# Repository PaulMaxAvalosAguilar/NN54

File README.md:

# Encoder2

Connecting science and technology with sport

If you want to achive change you must get power.Objectively know what you do, to control what you get, don't let things happen to you, make things happen.
Be stronger at any weight.

We understand that power is the only way to achieve change. Objectively know what you do, to control what you get. Be stronger at any weight

Incremental Optical Encoder

Project currently being worked by

Paul Max Avalos Aguilar

In the aiming of building an optical incremental encoder for vbt trainning

STUDIES THAT CONFIRM RELATIONSHIP BETWEEN VELOCITY AND %RM
Movement Velocity as a Measure of Loading Intensity in Resistance Training
https://www.researchgate.net/publication/41549227_Movement_Velocity_as_a_Measure_of_Loading_Intensity_in_Resistance_Training
There's a load-velocity relationship regardless of individual relative strength. These results confirm an inextricable relationshipbetween relative load and MPV:

1) evaluate maximal strength without the need to perform a 1RM test, or test of maximum number of repetitions to failure (XRM)
2) determine the %1RM that is being used as soon as the first repetition with any given load is performed
3) prescribe and monitor training load according to velocity, instead of percentages of 1RM or XRM.

STUDIES THAT CONFIRM RELATIONSHIP BETWEEN VELOCITY LOSS AND FATIGUE
Effect of loading on unintentional lifting velocity declines during single sets of repetitions to failure during upper and lower extremity muscle actions.
https://www.ncbi.nlm.nih.gov/pubmed/16944400
While average repetition velocity was recorded, a pattern of reduciton in the average velocity achieved during each repetition
was found.
This pattern of average velocity reduction indicates that for a given muscle action fatigue develops between each rep in a
given set in the form of velocity loss

Velocity Loss as a Variable for Monitoring Resistance Exercise
https://www.researchgate.net/publication/313686918_Velocity_Loss_as_a_Variable_for_Monitoring_Resistance_Exercise
There is a very close relationship was found between the relative loss of velocity in a set and the percentage of performed repetitions. Moreover, the percentage of performed repetitions for a given velocity loss showed a high absolute reliability. 

Movement velocity as a measure of level of effort during resistance exercise
https://www.researchgate.net/publication/318150104_Movement_velocity_as_a_measure_of_level_of_effort_during_resistance_exercise
By monitoring repetition velocity one can estimate with high accuracy the proximity of muscle failure and, therefore, to more objectively quantify the level of effort and fatigue being incurred during resistance training.

STUDIES THAT CONFIRM DIFFERENT FATIGUE PERCENTAGES TO GAINS STRENGTH
RESEARCHED APPLICATIONS OF VELOCITY BASED STRENGTH TRAINING
https://pdfs.semanticscholar.org/5f96/79c3f0f2d34478121d7cc33a50eb84dafb7a.pdf
minimizing velocity loss to an inferior to 20 percent can positively influence muscular strength, velocity losses of 35 percent an more can increase metabolites which
might produce longer recovery times

STUDIES THAT CONFIRM LIFTING AT MAX INTENDED SPEED PROVIDES BETTER ADAPTATIONS
Maximal intended velocity training induces greater gains in bench press performance than deliberately slower half-velocity training.
https://www.ncbi.nlm.nih.gov/pubmed/24734902
Lifting a given weight at maximum intended velocity provides significantly greater strength gains.
Strength gains can be maximised when repetitions are performed at maximal intended velocity

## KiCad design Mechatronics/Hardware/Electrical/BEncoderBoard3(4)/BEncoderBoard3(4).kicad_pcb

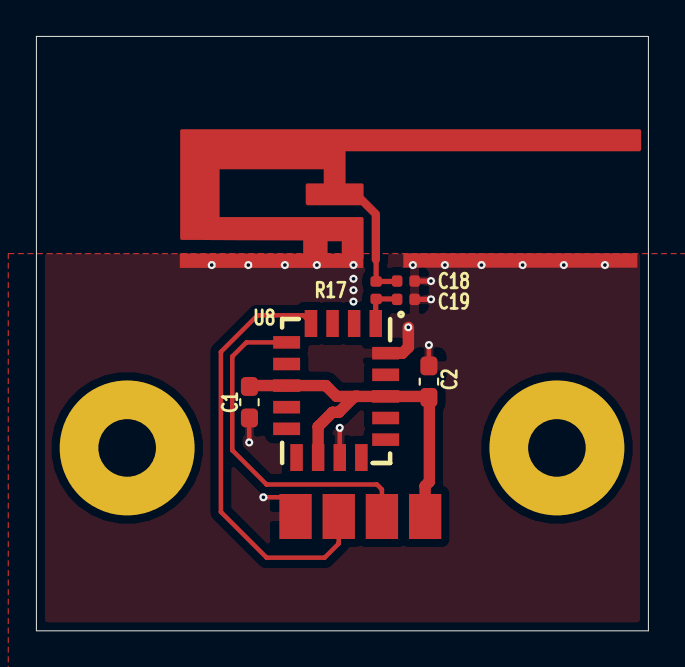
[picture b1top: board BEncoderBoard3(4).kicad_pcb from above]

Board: 4 copper layers, 34.0 x 33.0 mm, 9 parts (0 on the bottom side), 6 nets.

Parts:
AE1: LOGO; Antenna
C1: 1uF; C_0603_1608Metric_Pad1.05x0.95mm_HandSolder
C2: 10uF; C_0603_1608Metric_Pad1.05x0.95mm_HandSolder
C18, C19: C_Rf; C_0402_1005Metric
J1: Conn_01x04_Male; SolderWirePad_1x04_SMD_5x10mm_copy
R17: L_Rf; L_0402_1005Metric
U8: RN4871U
e: MountingHole_3.2mm_M3_Pad

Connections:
+3V3: C1.1, C2.1, J1.4, U8.7, U8.11, U8.16
GND: AE1.2, C1.2, C2.2, C18.2, C19.2, J1.1, U8.12, U8.18
unnamed: C18.1, R17.2
unnamed: C19.1, R17.1, U8.1
unnamed: J1.2, U8.4
unnamed: J1.3, U8.5

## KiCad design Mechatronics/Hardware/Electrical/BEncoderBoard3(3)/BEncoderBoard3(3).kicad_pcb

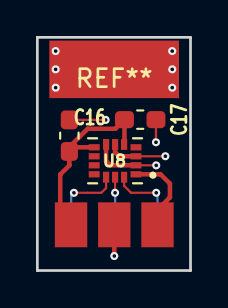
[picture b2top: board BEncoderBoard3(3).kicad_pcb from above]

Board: 2 copper layers, 8.5 x 13.0 mm, 4 parts (0 on the bottom side), 6 nets.

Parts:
C16, C17: 100nF; C_0603_1608Metric_Pad1.05x0.95mm_HandSolder
J1: Conn_01x06_Male; SolderWirePad_1x06_SMD_5x10mm
U8: LSM6DSRX

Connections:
+3V3: C16.2, C17.2, J1.6, U8.5, U8.8
/CS: J1.1, U8.12
/SCL: J1.2, U8.13
/SDA: J1.3, U8.14
/SDO: J1.4, U8.1
GND: C16.1, C17.1, J1.5, U8.2, U8.3, U8.6, U8.7

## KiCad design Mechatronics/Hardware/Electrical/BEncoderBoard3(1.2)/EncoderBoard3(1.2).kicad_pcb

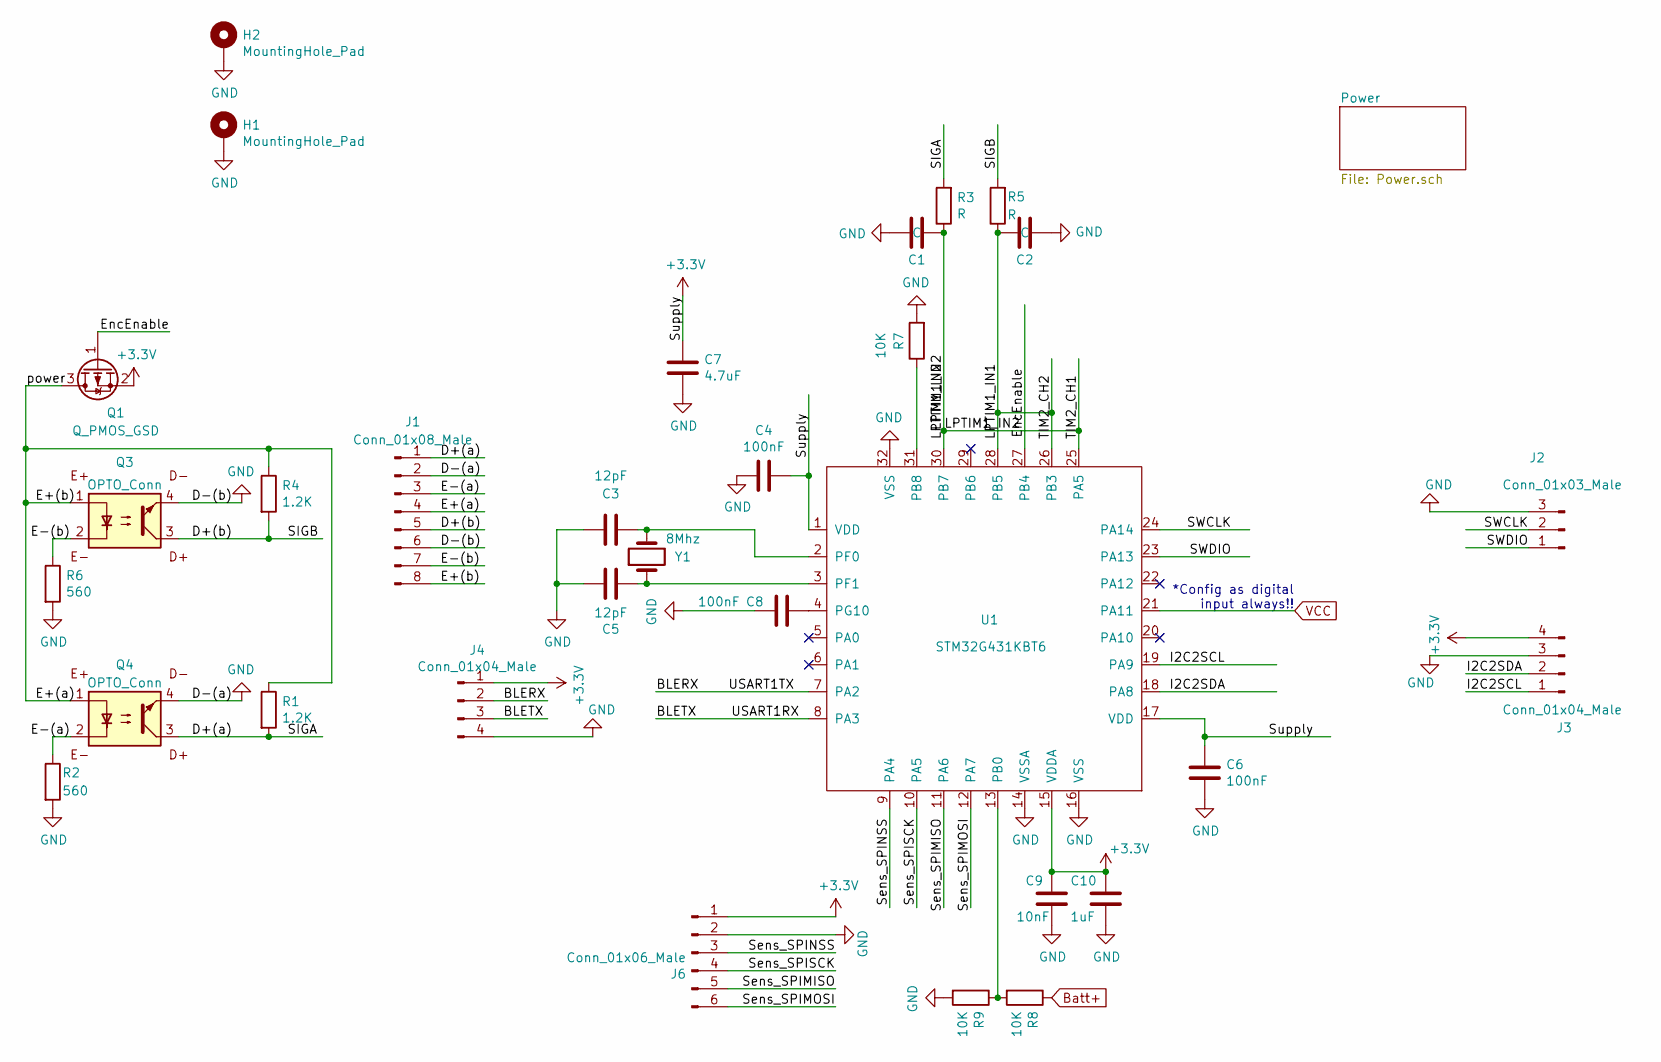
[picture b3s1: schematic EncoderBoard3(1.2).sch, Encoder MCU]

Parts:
C1, C2: C; C_0603_1608Metric_Pad1.05x0.95mm_HandSolder
C3, C5: 12pF; C_0603_1608Metric_Pad1.05x0.95mm_HandSolder
C4, C6, C8: 100nF; C_0603_1608Metric_Pad1.05x0.95mm_HandSolder
C7: 4.7uF; C_0603_1608Metric_Pad1.05x0.95mm_HandSolder
C9: 10nF; C_0603_1608Metric_Pad1.05x0.95mm_HandSolder
C10: 1uF; C_0603_1608Metric_Pad1.05x0.95mm_HandSolder
H1, H2: MountingHole_Pad; MountingHole_3.2mm_M3_Pad
J1: Conn_01x08_Male; JST_EH_B8B-EH-A_1x08_P2.50mm_Vertical
J2: Conn_01x03_Male; PinHeader_1x03_P2.54mm_Vertical
J3, J4: Conn_01x04_Male; JST_EH_B4B-EH-A_1x04_P2.50mm_Vertical
J6: Conn_01x06_Male; JST_EH_B6B-EH-A_1x06_P2.50mm_Vertical
Q1: Q_PMOS_GSD; SOT-23
Q3, Q4: OPTO_Conn
R1, R4: 1.2K; R_0603_1608Metric_Pad1.05x0.95mm_HandSolder
R2, R6: 560; R_0603_1608Metric_Pad1.05x0.95mm_HandSolder
R3, R5: R; R_0603_1608Metric_Pad1.05x0.95mm_HandSolder
R7, R8, R9: 10K; R_0603_1608Metric_Pad1.05x0.95mm_HandSolder
U1: STM32G431KBT6; LQFP-32_7x7mm_P0.8mm
Y1: 8Mhz; Crystal_HC49-U_Vertical

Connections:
+3V3: C4.1, C6.1, C7.1, C9.1, C10.1, J3.4, J4.1, J6.1, Q1.2 (S), U1.1 (VDD), U1.15 (VDDA), U1.17 (VDD); also elsewhere on the board
/BLERX: J4.2, U1.7 (PA2)
/BLETX: J4.3, U1.8 (PA3)
/D+(a): J1.1, Q4.3, R1.2, R3.2
/D+(b): J1.5, Q3.3, R4.2, R5.2
/E+(a): J1.4, J1.8, Q1.3 (D), Q3.1, Q4.1, R1.1, R4.1
/E-(a): J1.3, Q4.2, R2.1
/E-(b): J1.7, Q3.2, R6.1
/EncEnable: Q1.1 (G), U1.27 (PB4)
/I2C2SCL: J3.1, U1.19 (PA9)
/I2C2SDA: J3.2, U1.18 (PA8)
/LPTIM1_IN1: C2.2, R5.1, U1.26 (PB3), U1.28 (PB5)
/LPTIM1_IN2: C1.1, R3.1, U1.25 (PA5), U1.30 (PB7)
/SWCLK: J2.2, U1.24 (PA14)
/SWDIO: J2.1, U1.23 (PA13)
/Sens_SPIMISO: J6.5, U1.11 (PA6)
/Sens_SPIMOSI: J6.6, U1.12 (PA7)
/Sens_SPINSS: J6.3, U1.9 (PA4)
/Sens_SPISCK: J6.4, U1.10 (PA5)
Batt+: R8.1; also elsewhere on the board
GND: C1.2, C2.1, C3.1, C4.2, C5.1, C6.2, C7.2, C8.2, C9.2, C10.2, H1.1, H2.1, J1.2, J1.6, J2.3, J3.3, J4.4, J6.2, Q3.4, Q4.4, R2.2, R6.2, R7.2, R9.2, U1.14 (VSSA), U1.16 (VSS), U1.32 (VSS); also elsewhere on the board
unnamed: C3.2, U1.2 (PF0), Y1.2
unnamed: C5.2, U1.3 (PF1), Y1.1
unnamed: C8.1, U1.4 (PG10)
unnamed: R7.1, U1.31 (PB8)
unnamed: R8.2, R9.1, U1.13 (PB0)
VCC: U1.21 (PA11); also elsewhere on the board

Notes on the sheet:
*Config as digital input always!!

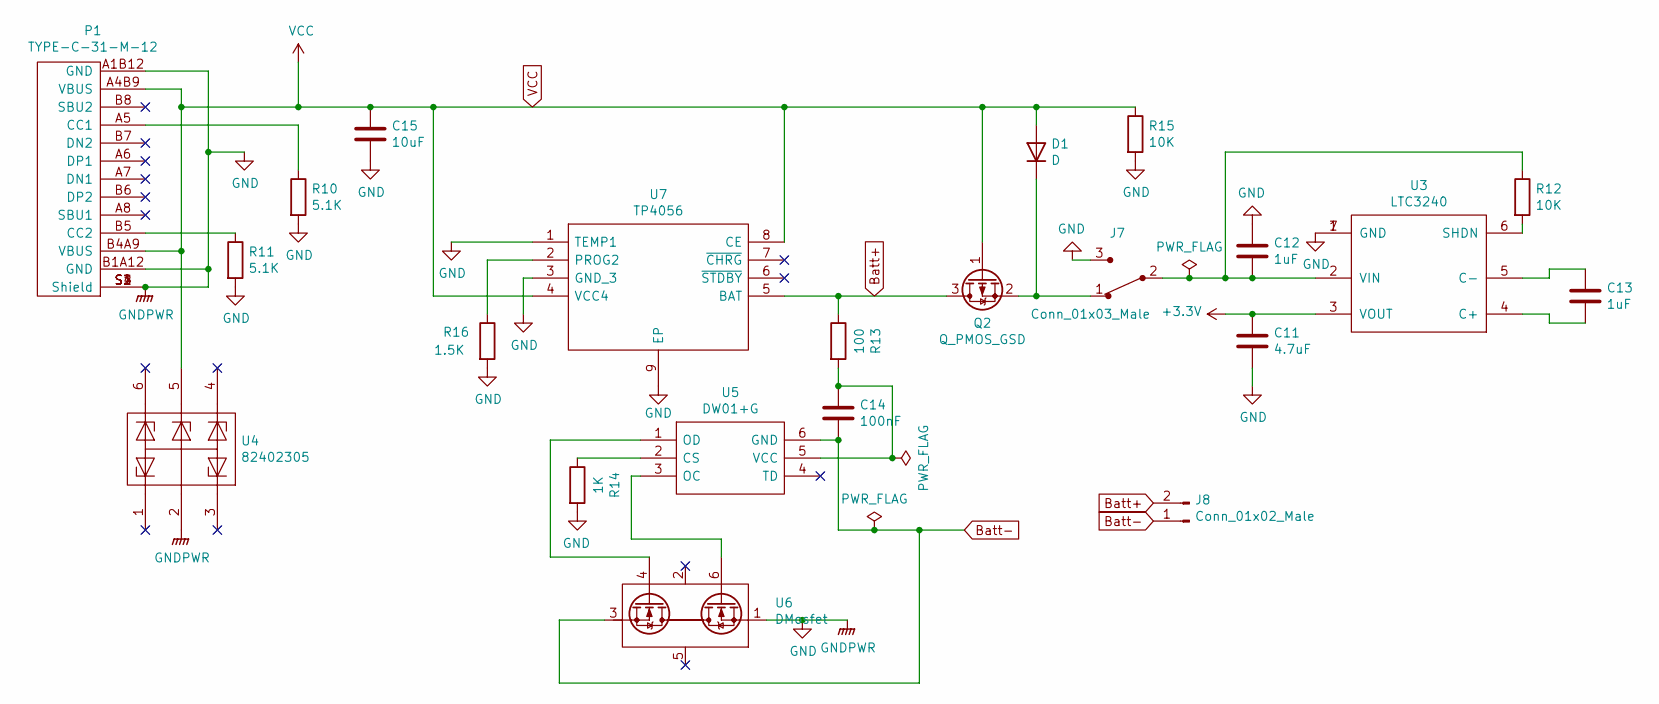
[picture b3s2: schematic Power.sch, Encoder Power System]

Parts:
C11: 4.7uF; C_0603_1608Metric_Pad1.05x0.95mm_HandSolder
C12, C13: 1uF; C_0603_1608Metric_Pad1.05x0.95mm_HandSolder
C14: 100nF; C_0603_1608Metric_Pad1.05x0.95mm_HandSolder
C15: 10uF; C_0603_1608Metric_Pad1.05x0.95mm_HandSolder
D1: D; D_SMA
J7: Conn_01x03_Male; JST_EH_B3B-EH-A_1x03_P2.50mm_Vertical; MPN EG1218; Digi-Key_PN EG1903-ND
J8: Conn_01x02_Male; JST_EH_B2B-EH-A_1x02_P2.50mm_Vertical
P1: TYPE-C-31-M-12; HRO_TYPE-C-31-M-12
Q2: Q_PMOS_GSD; SOT-23
R10, R11: 5.1K; R_0603_1608Metric_Pad1.05x0.95mm_HandSolder
R12, R15: 10K; R_0603_1608Metric_Pad1.05x0.95mm_HandSolder
R13: 100; R_0603_1608Metric_Pad1.05x0.95mm_HandSolder
R14: 1K; R_0603_1608Metric_Pad1.05x0.95mm_HandSolder
R16: 1.5K; R_0603_1608Metric_Pad1.05x0.95mm_HandSolder
U3: LTC3240; DFN-6_DC
U4: 82402305; Sot-23(6)
U5: DW01+G; Sot-23(6); Manufacturer_Part_Number DW01+G
U6: DMosfet; Sot-23(6)
U7: TP4056; Sop(8); Manufacturer_Part_Number TP4056

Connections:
+3V3: C11.1, U3.3 (VOUT); also elsewhere on the board
Batt+: J8.2, Q2.3 (D), R13.1, U7.5 (BAT); also elsewhere on the board
Batt-: C14.2, J8.1, U5.6 (GND), U6.3 (S)
GND: C11.2, C12.1, C15.2, J7.3, P1.A1B12 (GND), P1.B1A12 (GND), P1.S1 (Shield), P1.S2 (Shield), P1.S3 (Shield), P1.S4 (Shield), R10.2, R11.2, R14.2, R15.2, R16.2, U3.1 (GND), U3.7 (GND), U4.2, U6.1 (S), U7.1 (TEMP1), U7.3 (GND_3), U7.9 (EP); also elsewhere on the board
unnamed: C12.2, J7.2, R12.1, U3.2 (VIN)
unnamed: C13.1, U3.5 (C-)
unnamed: C13.2, U3.4 (C+)
unnamed: C14.1, R13.2, U5.5 (VCC)
unnamed: D1.1 (K), J7.1, Q2.2 (S)
unnamed: P1.A5 (CC1), R10.1
unnamed: P1.B5 (CC2), R11.1
unnamed: R12.2, U3.6 (SHDN)
unnamed: R14.1, U5.2 (CS)
unnamed: R16.1, U7.2 (PROG2)
unnamed: U5.1 (OD), U6.4 (G)
unnamed: U5.3 (OC), U6.6 (G)
VCC: C15.1, D1.2 (A), P1.A4B9 (VBUS), P1.B4A9 (VBUS), Q2.1 (G), R15.1, U4.5, U7.4 (VCC4), U7.8 (CE); also elsewhere on the board

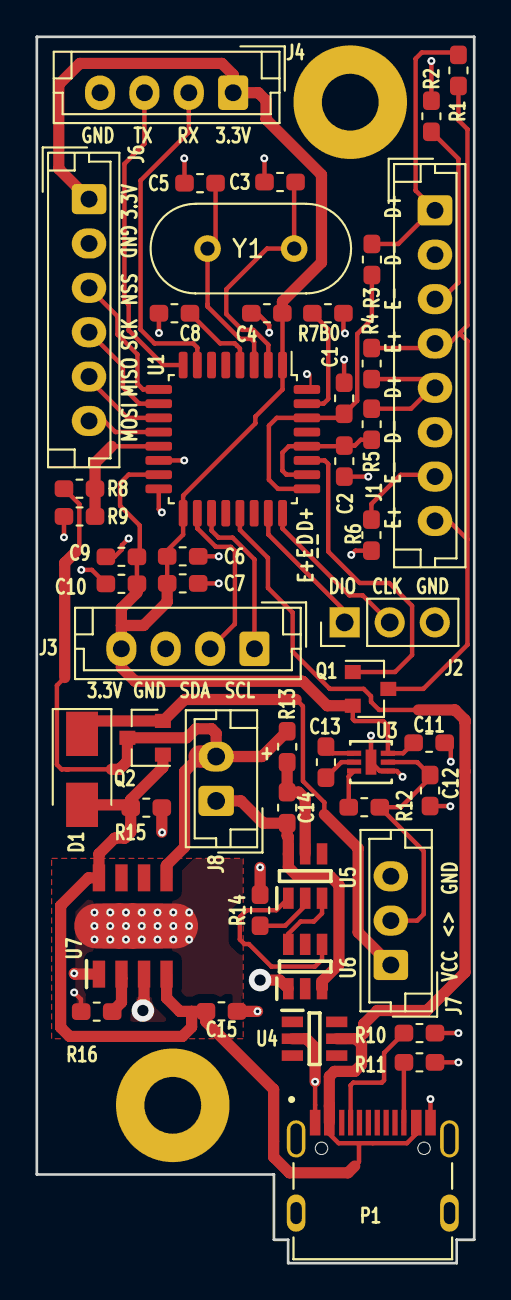
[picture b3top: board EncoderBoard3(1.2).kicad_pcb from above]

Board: 2 copper layers, 24.6 x 69.1 mm, 51 parts (0 on the bottom side), 40 nets.

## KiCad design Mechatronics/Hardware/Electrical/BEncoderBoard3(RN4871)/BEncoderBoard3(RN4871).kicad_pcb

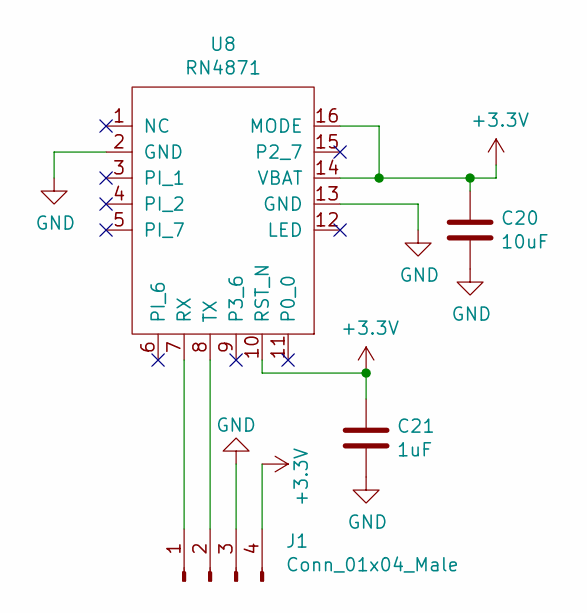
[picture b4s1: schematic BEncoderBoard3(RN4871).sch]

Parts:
C20: 10uF; C_0603_1608Metric_Pad1.05x0.95mm_HandSolder
C21: 1uF; C_0603_1608Metric_Pad1.05x0.95mm_HandSolder
J1: Conn_01x04_Male; SolderWirePad_1x04_SMD_5x10mm_copy
U8: RN4871; Bluetooth_Module_RN4871

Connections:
+3V3: C20.1, C21.1, J1.4, U8.10 (RST_N), U8.14 (VBAT), U8.16 (MODE)
GND: C20.2, C21.2, J1.3, U8.2 (GND), U8.13 (GND)
unnamed: J1.1, U8.7 (RX)
unnamed: J1.2, U8.8 (TX)

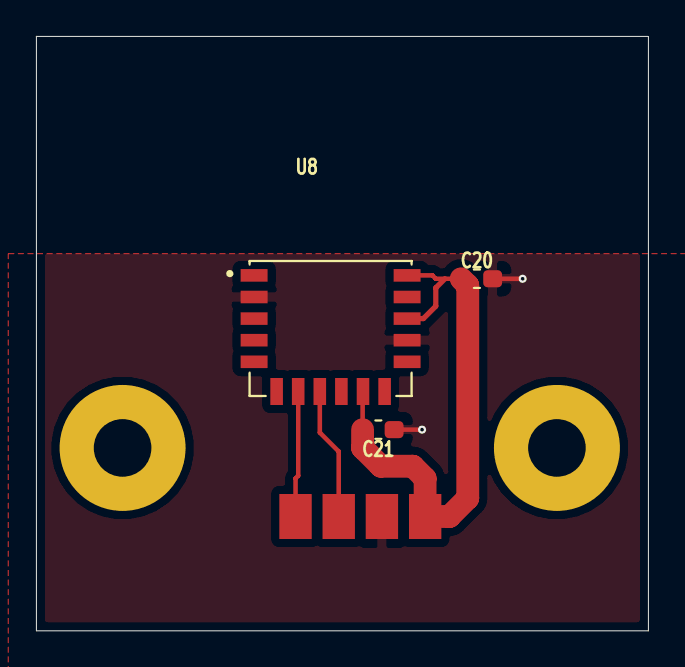
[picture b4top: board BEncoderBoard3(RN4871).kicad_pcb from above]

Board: 4 copper layers, 34.0 x 33.0 mm, 4 parts (0 on the bottom side), 4 nets.

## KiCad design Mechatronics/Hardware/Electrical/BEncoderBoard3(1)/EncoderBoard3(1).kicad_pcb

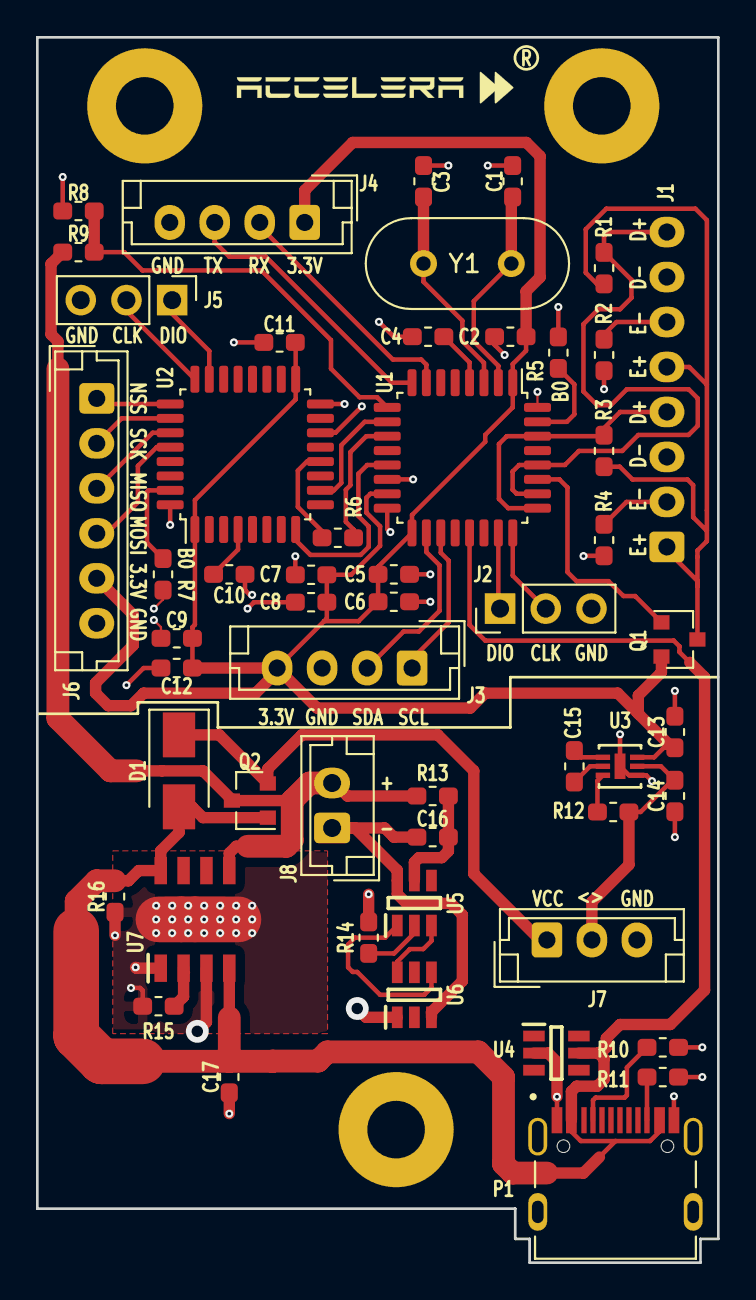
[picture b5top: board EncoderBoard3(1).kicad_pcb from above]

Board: 2 copper layers, 37.8 x 68.1 mm, 53 parts (1 on the bottom side), 46 nets.

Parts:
C1, C3: 12pF; C_0603_1608Metric_Pad1.05x0.95mm_HandSolder
C2, C4, C5, C9, C10, C11, C16: 100nF; C_0603_1608Metric_Pad1.05x0.95mm_HandSolder
C6, C12, C13: 4.7uF; C_0603_1608Metric_Pad1.05x0.95mm_HandSolder
C7: 10nF; C_0603_1608Metric_Pad1.05x0.95mm_HandSolder
C8, C14, C15: 1uF; C_0603_1608Metric_Pad1.05x0.95mm_HandSolder
C17: 10uF; C_0603_1608Metric_Pad1.05x0.95mm_HandSolder
D1: D; D_SMA
J1: Conn_01x08_Male; JST_EH_B8B-EH-A_1x08_P2.50mm_Vertical
J2, J5: Conn_01x03_Male; PinHeader_1x03_P2.54mm_Vertical
J3, J4: Conn_01x04_Male; JST_EH_B4B-EH-A_1x04_P2.50mm_Vertical
J6: Conn_01x06_Male; JST_EH_B6B-EH-A_1x06_P2.50mm_Vertical
J7: Conn_01x03_Male; JST_EH_B3B-EH-A_1x03_P2.50mm_Vertical
J8: Conn_01x02_Male; JST_EH_B2B-EH-A_1x02_P2.50mm_Vertical
P1: TYPE-C-31-M-12; HRO_TYPE-C-31-M-12
Q1, Q2: Q_PMOS_GSD; SOT-23
R1, R3: 1.2K; R_0603_1608Metric_Pad1.05x0.95mm_HandSolder
R2, R4: 560; R_0603_1608Metric_Pad1.05x0.95mm_HandSolder
R5, R7, R8, R9, R12, R16: 10K; R_0603_1608Metric_Pad1.05x0.95mm_HandSolder
R6, R14: 1K; R_0603_1608Metric_Pad1.05x0.95mm_HandSolder
R10: 5.1k; R_0603_1608Metric_Pad1.05x0.95mm_HandSolder
R11: 5.1K; R_0603_1608Metric_Pad1.05x0.95mm_HandSolder
R13: 100; R_0603_1608Metric_Pad1.05x0.95mm_HandSolder
R15: 1.5K; R_0603_1608Metric_Pad1.05x0.95mm_HandSolder
U1, U2: STM32G431KBT6; LQFP-32_7x7mm_P0.8mm
U3: LTC3240; DFN-6_DC
U4: 82402305; Sot-23(6)
U5: DW01+G; Sot-23(6)
U6: DMosfet; Sot-23(6)
U7: TP4056; Sop(8)
Y1: 8Mhz; Crystal_HC49-U_Vertical

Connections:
+3V3: C2.1, C5.1, C6.1, C7.1, C8.1, C9.1, C11.1, C12.1, C13.1, J3.4, J4.1, J6.5, Q1.2, U1.1, U1.15, U1.17, U2.1, U2.17, U3.3
/BLERX: J4.2, U1.7
/BLETX: J4.3, U1.8
/D+(a): J1.8, R1.2, U1.26, U1.28
/D+(b): J1.4, R3.2, U1.25, U1.30
/Data: U1.13, U2.8
/E+(a): J1.1, J1.5, Q1.3, R1.1, R3.1
/E-(a): J1.6, R2.1
/E-(b): J1.2, R4.1
/EncEnable: Q1.1, U1.27
/I2C2SCL: J3.1, U1.19
/I2C2SDA: J3.2, U1.18
/SPI1MISO: R6.2, U1.11
/SPI1SCK: U1.10, U2.10
/SWCLK: J2.2, U1.24
/SWDIO: J2.1, U1.23
/Sens_SPI1MOSI: R6.1, U2.12
/Sens_SPI3MISO: J6.3, U2.27
/Sens_SPI3MOSI: J6.4, U2.28
/Sens_SPI3NSS: J6.1, U2.25
/Sens_SPI3SCK: J6.2, U2.26
/Sens_SWCLK: J5.2, U2.24
/Sens_SWDIO: J5.1, U2.23
Batt+: J8.2, Q2.3, R9.1, R13.1, U7.5
Batt-: C16.2, J8.1, U5.6, U6.3
GND: C1.1, C2.2, C3.1, C4.2, C5.2, C6.2, C7.2, C8.2, C9.2, C10.2, C11.2, C12.2, C13.2, C14.1, C17.2, J1.3, J1.7, J2.3, J3.3, J4.4, J5.3, J6.6, J7.3, P1.A1B12, P1.B1A12, P1.S1, P1.S2, P1.S3, P1.S4, R2.2, R4.2, R5.2, R7.2, R8.2, R10.2, R11.2, R14.2, R15.2, R16.2, U1.14, U1.16, U1.32, U2.14, U2.16, U2.32, U3.1, U3.7, U4.2, U6.1, U7.1, U7.3, U7.9
unnamed: C1.2, U1.2, Y1.2
unnamed: C3.2, U1.3, Y1.1
unnamed: C4.1, U1.4
unnamed: C10.1, U2.4
unnamed: C14.2, J7.2, R12.1, U3.2
unnamed: C15.1, U3.5
unnamed: C15.2, U3.4
unnamed: C16.1, R13.2, U5.5
unnamed: D1.1, J7.1, Q2.2
unnamed: P1.A5, R10.1
unnamed: P1.B5, R11.1
unnamed: R5.1, U1.31
unnamed: R7.1, U2.31
unnamed: R8.1, R9.2, U1.9
unnamed: R12.2, U3.6
unnamed: R14.1, U5.2
unnamed: R15.1, U7.2
unnamed: U5.1, U6.4
unnamed: U5.3, U6.6
VCC: C17.1, D1.2, P1.A4B9, P1.B4A9, Q2.1, R16.1, U1.21, U4.5, U7.4, U7.8

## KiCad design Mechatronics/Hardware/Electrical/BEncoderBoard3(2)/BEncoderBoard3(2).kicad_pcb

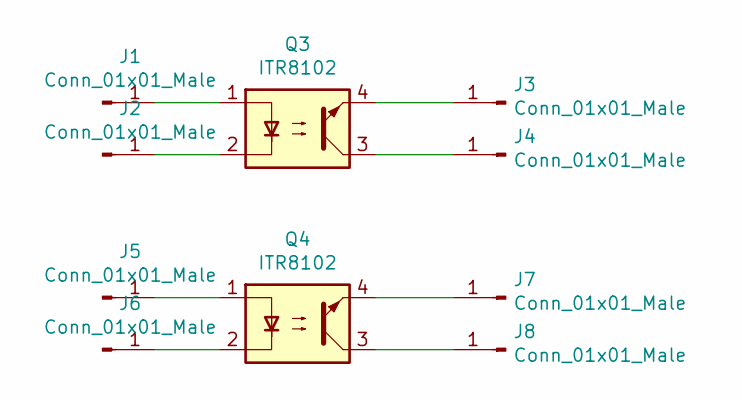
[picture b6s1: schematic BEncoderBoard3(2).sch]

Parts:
J1, J2, J3, J4, J5, J6, J7, J8: Conn_01x01_Male; PinHeader_1x01_P2.54mm_Vertical_NO3D
Q3, Q4: ITR8102; itr8102

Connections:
unnamed: J1.1, Q3.1
unnamed: J2.1, Q3.2
unnamed: J3.1, Q3.4
unnamed: J4.1, Q3.3
unnamed: J5.1, Q4.1
unnamed: J6.1, Q4.2
unnamed: J7.1, Q4.4
unnamed: J8.1, Q4.3

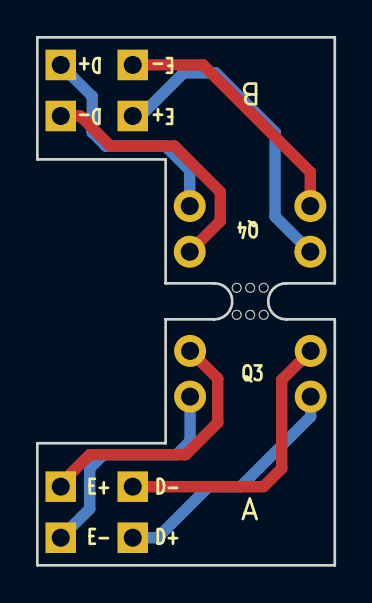
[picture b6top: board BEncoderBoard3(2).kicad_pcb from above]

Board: 2 copper layers, 16.5 x 29.3 mm, 11 parts (0 on the bottom side), 8 nets.

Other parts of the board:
mouse-bite-2mm-slot: VAL**; mouse-bite-2mm-slot

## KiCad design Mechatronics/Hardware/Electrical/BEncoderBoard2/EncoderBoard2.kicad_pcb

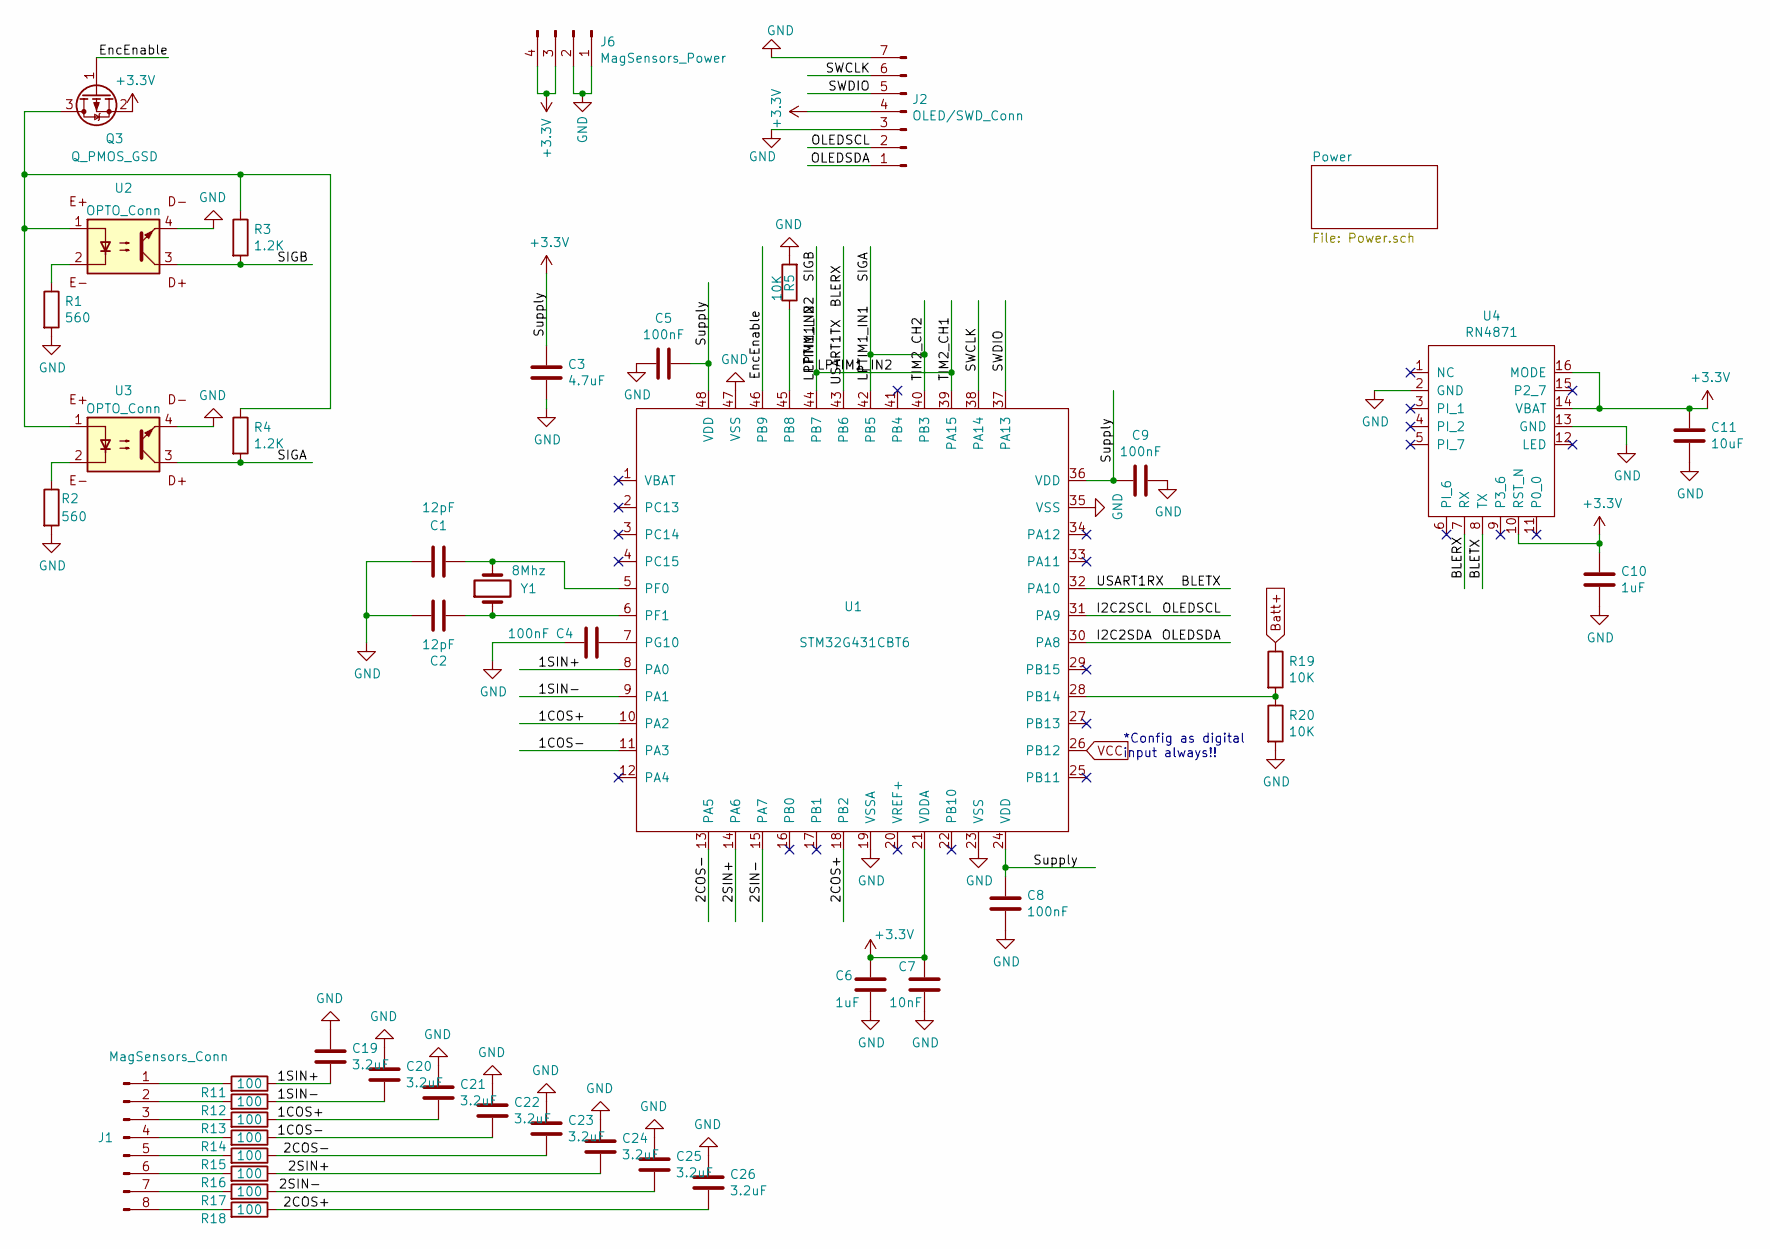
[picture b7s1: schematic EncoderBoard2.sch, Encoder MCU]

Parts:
C1, C2: 12pF; C_0603_1608Metric_Pad1.05x0.95mm_HandSolder
C3: 4.7uF; C_0603_1608Metric_Pad1.05x0.95mm_HandSolder
C4, C5, C8, C9: 100nF; C_0603_1608Metric_Pad1.05x0.95mm_HandSolder
C6, C10: 1uF; C_0603_1608Metric_Pad1.05x0.95mm_HandSolder
C7: 10nF; C_0603_1608Metric_Pad1.05x0.95mm_HandSolder
C11: 10uF; C_0603_1608Metric_Pad1.05x0.95mm_HandSolder
C19, C20, C21, C22, C23, C24, C25, C26: 3.2uF; C_0603_1608Metric_Pad1.05x0.95mm_HandSolder
J1: MagSensors_Conn; PinHeader_1x08_P2.54mm_Vertical
J2: OLED/SWD_Conn; PinHeader_1x07_P2.54mm_Vertical
J6: MagSensors_Power; PinHeader_2x02_P2.54mm_Vertical
Q3: Q_PMOS_GSD; SOT-23
R1, R2: 560; R_0603_1608Metric_Pad1.05x0.95mm_HandSolder
R3, R4: 1.2K; R_0603_1608Metric_Pad1.05x0.95mm_HandSolder
R5, R19, R20: 10K; R_0603_1608Metric_Pad1.05x0.95mm_HandSolder
R11, R12, R13, R14, R15, R16, R17, R18: 100; R_0603_1608Metric_Pad1.05x0.95mm_HandSolder
U1: STM32G431CBT6; LQFP-48_7x7mm_P0.5mm
U2, U3: OPTO_Conn; PinHeader_2x02_P2.54mm_Vertical
U4: RN4871; Bluetooth_Module_RN4871
Y1: 8Mhz; Crystal_HC49-U_Vertical

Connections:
+3V3: C3.1, C5.1, C6.1, C7.1, C8.1, C9.2, C10.1, C11.1, J2.4, J6.3, J6.4, Q3.2 (S), U1.21 (VDDA), U1.24 (VDD), U1.36 (VDD), U1.48 (VDD), U4.10 (RST_N), U4.14 (VBAT), U4.16 (MODE); also elsewhere on the board
/1COS+: C21.2, R13.1, U1.10 (PA2)
/1COS-: C22.2, R14.1, U1.11 (PA3)
/1SIN+: C19.2, R11.1, U1.8 (PA0)
/1SIN-: C20.2, R12.1, U1.9 (PA1)
/2COS+: C26.2, R18.1, U1.18 (PB2)
/2COS-: C23.2, R15.1, U1.13 (PA5)
/2SIN+: C24.2, R16.1, U1.14 (PA6)
/2SIN-: C25.2, R17.1, U1.15 (PA7)
/BLERX: U1.43 (PB6), U4.7 (RX)
/BLETX: U1.32 (PA10), U4.8 (TX)
/EncEnable: Q3.1 (G), U1.46 (PB9)
/I2C2SCL: J2.2, U1.31 (PA9)
/I2C2SDA: J2.1, U1.30 (PA8)
/LPTIM1_IN1: R4.2, U1.40 (PB3), U1.42 (PB5), U3.3
/LPTIM1_IN2: R3.2, U1.39 (PA15), U1.44 (PB7), U2.3
/SWCLK: J2.6, U1.38 (PA14)
/SWDIO: J2.5, U1.37 (PA13)
Batt+: R19.1; also elsewhere on the board
GND: C1.1, C2.1, C3.2, C4.2, C5.2, C6.2, C7.2, C8.2, C9.1, C10.2, C11.2, C19.1, C20.1, C21.1, C22.1, C23.1, C24.1, C25.1, C26.1, J2.3, J2.7, J6.1, J6.2, R1.2, R2.2, R5.2, R20.2, U1.19 (VSSA), U1.23 (VSS), U1.35 (VSS), U1.47 (VSS), U2.4, U3.4, U4.2 (GND), U4.13 (GND); also elsewhere on the board
unnamed: C1.2, U1.5 (PF0), Y1.2
unnamed: C2.2, U1.6 (PF1), Y1.1
unnamed: C4.1, U1.7 (PG10)
unnamed: J1.1, R11.2
unnamed: J1.2, R12.2
unnamed: J1.3, R13.2
unnamed: J1.4, R14.2
unnamed: J1.5, R15.2
unnamed: J1.6, R16.2
unnamed: J1.7, R17.2
unnamed: J1.8, R18.2
unnamed: Q3.3 (D), R3.1, R4.1, U2.1, U3.1
unnamed: R1.1, U2.2
unnamed: R2.1, U3.2
unnamed: R5.1, U1.45 (PB8)
unnamed: R19.2, R20.1, U1.28 (PB14)
VCC: U1.26 (PB12); also elsewhere on the board

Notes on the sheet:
*Config as digital input always!!

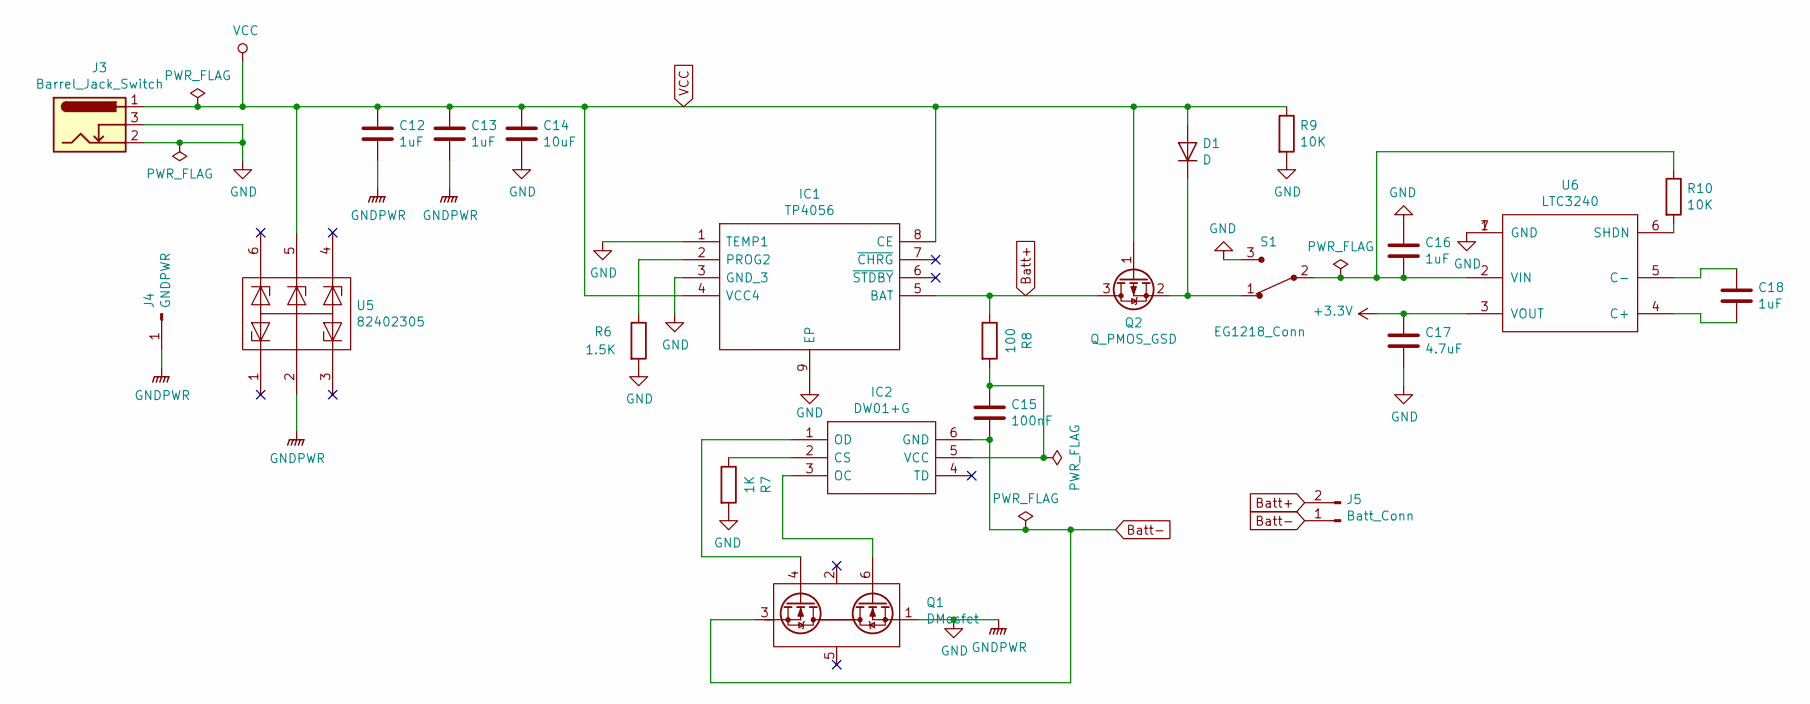
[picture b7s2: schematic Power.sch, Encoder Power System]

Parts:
C12, C13, C16, C18: 1uF; C_0603_1608Metric_Pad1.05x0.95mm_HandSolder
C14: 10uF; C_0603_1608Metric_Pad1.05x0.95mm_HandSolder
C15: 100nF; C_0603_1608Metric_Pad1.05x0.95mm_HandSolder
C17: 4.7uF; C_0603_1608Metric_Pad1.05x0.95mm_HandSolder
D1: D; D_SMA
IC1: TP4056; Sop(8); Manufacturer_Part_Number TP4056
IC2: DW01+G; Sot-23(6); Manufacturer_Part_Number DW01+G
J3: Barrel_Jack_Switch; BarrelJack_Horizontal
J4: GNDPWR; PinHeader_1x01_P2.54mm_Vertical
J5: Batt_Conn; PinHeader_1x02_P2.54mm_Vertical
Q1: DMosfet; Sot-23(6)
Q2: Q_PMOS_GSD; SOT-23
R6: 1.5K; R_0603_1608Metric_Pad1.05x0.95mm_HandSolder
R7: 1K; R_0603_1608Metric_Pad1.05x0.95mm_HandSolder
R8: 100; R_0603_1608Metric_Pad1.05x0.95mm_HandSolder
R9, R10: 10K; R_0603_1608Metric_Pad1.05x0.95mm_HandSolder
S1: EG1218_Conn; PinHeader_1x03_P2.54mm_Vertical; MPN EG1218; Digi-Key_PN EG1903-ND
U5: 82402305; Sot-23(6)
U6: LTC3240; DFN-6_DC

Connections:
+3V3: C17.1, U6.3 (VOUT); also elsewhere on the board
Batt+: IC1.5 (BAT), J5.2, Q2.3 (D), R8.1; also elsewhere on the board
Batt-: C15.2, IC2.6 (GND), J5.1, Q1.3 (S)
GND: C12.2, C13.2, C14.2, C16.1, C17.2, IC1.1 (TEMP1), IC1.3 (GND_3), IC1.9 (EP), J3.2, J3.3, J4.1, Q1.1 (S), R6.2, R7.2, R9.2, S1.3, U5.2, U6.1 (GND), U6.7 (GND); also elsewhere on the board
unnamed: C15.1, IC2.5 (VCC), R8.2
unnamed: C16.2, R10.1, S1.2, U6.2 (VIN)
unnamed: C18.1, U6.5 (C-)
unnamed: C18.2, U6.4 (C+)
unnamed: D1.1 (K), Q2.2 (S), S1.1
unnamed: IC1.2 (PROG2), R6.1
unnamed: IC2.1 (OD), Q1.4 (G)
unnamed: IC2.2 (CS), R7.1
unnamed: IC2.3 (OC), Q1.6 (G)
unnamed: R10.2, U6.6 (SHDN)
VCC: C12.1, C13.1, C14.1, D1.2 (A), IC1.4 (VCC4), IC1.8 (CE), J3.1, Q2.1 (G), R9.1, U5.5; also elsewhere on the board

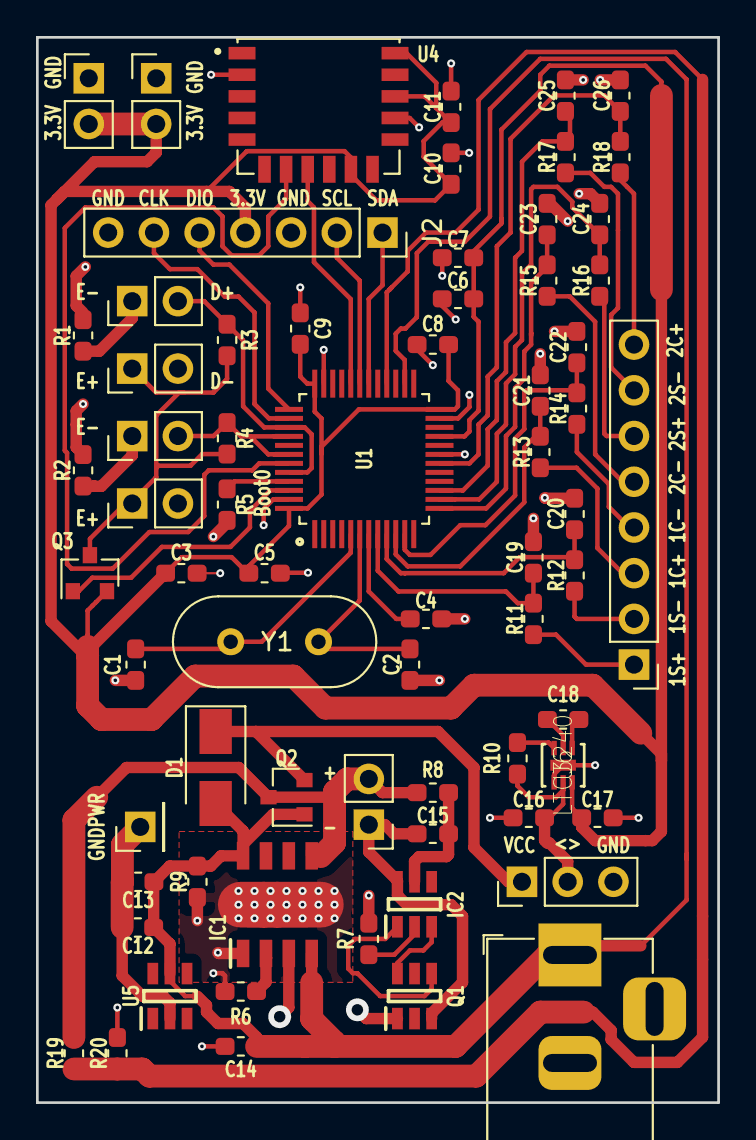
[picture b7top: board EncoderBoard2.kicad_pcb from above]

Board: 2 copper layers, 37.8 x 59.2 mm, 66 parts (0 on the bottom side), 48 nets.

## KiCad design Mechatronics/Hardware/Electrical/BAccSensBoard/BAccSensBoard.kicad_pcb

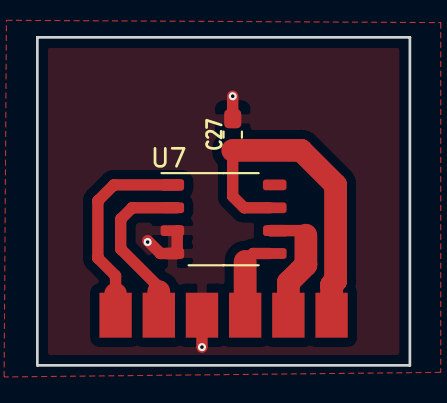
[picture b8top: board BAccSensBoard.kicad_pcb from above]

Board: 2 copper layers, 20.7 x 18.2 mm, 3 parts (0 on the bottom side), 6 nets.

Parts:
C27: 100nF; C_0603_1608Metric_Pad1.05x0.95mm_HandSolder
J7: Conn_01x06_Male; SolderWirePad_1x01_SMD_5x10mm
U7: TLE5009; SO-8_3.9x4.9mm_P1.27mm

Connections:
/COS_N: J7.2, U7.2
/COS_P: J7.1, U7.1
/SIN_N: J7.5, U7.6
/SIN_P: J7.4, U7.5
/VDD: C27.1, J7.6, U7.7
GND: C27.2, J7.3, U7.3, U7.4

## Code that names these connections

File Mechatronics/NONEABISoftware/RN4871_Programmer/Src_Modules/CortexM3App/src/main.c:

#include <libopencm3/stm32/rcc.h>
#include <libopencm3/stm32/gpio.h>
#include <libopencm3/stm32/usart.h>
#include <stdio.h>
#include <string.h>

extern void initialise_monitor_handles(void);

static void configurePeriphereals(void){

  rcc_periph_clock_enable(RCC_AFIO);    // I2C UART ADC EXTI
  rcc_periph_clock_enable(RCC_GPIOB);	// I2C TIM2 UART
  rcc_periph_clock_enable(RCC_USART1);  // UART

  //UART
  /* Setup GPIO pin GPIO_USART1_RE_TX on GPIO port B for transmit. */
  gpio_set_mode(GPIOB, GPIO_MODE_OUTPUT_50_MHZ,
		GPIO_CNF_OUTPUT_ALTFN_PUSHPULL, GPIO6);

  /* Setup GPIO pin GPIO_USART1_RE_RX on GPIO port B for receive. */
  gpio_set_mode(GPIOB, GPIO_MODE_INPUT,
		GPIO_CNF_INPUT_PULL_UPDOWN , GPIO7);
  gpio_clear(GPIOB, GPIO7);

  /* Setup UART parameters. */
  usart_set_baudrate(USART1, 115200);
  usart_set_databits(USART1, 8);
  usart_set_stopbits(USART1, USART_STOPBITS_1);
  usart_set_parity(USART1, USART_PARITY_NONE);
  usart_set_flow_control(USART1, USART_FLOWCONTROL_NONE);
  //  usart_set_flow_control(USART1,USART_FLOWCONTROL_RTS_CTS);
  usart_set_mode(USART1, USART_MODE_TX_RX);
  //UART

  gpio_primary_remap(AFIO_MAPR_SWJ_CFG_JTAG_OFF_SW_ON,
		     AFIO_MAPR_I2C1_REMAP |  //I2C PB8 + PB9
		     AFIO_MAPR_TIM2_REMAP_PARTIAL_REMAP1 |
		     AFIO_MAPR_USART1_REMAP  ); //USART PB6 + PB7

    usart_enable(USART1);//Enable USART

}

int main(void)
{
  rcc_clock_setup_in_hse_8mhz_out_72mhz();// For "blue pill"
  configurePeriphereals();
    initialise_monitor_handles();
  for(;;){

    for(unsigned int i = 0; i < 100000; i++);
    usart_send_blocking(USART1,'h');
    printf("HOLA\n");


  }

  return 0;
}
